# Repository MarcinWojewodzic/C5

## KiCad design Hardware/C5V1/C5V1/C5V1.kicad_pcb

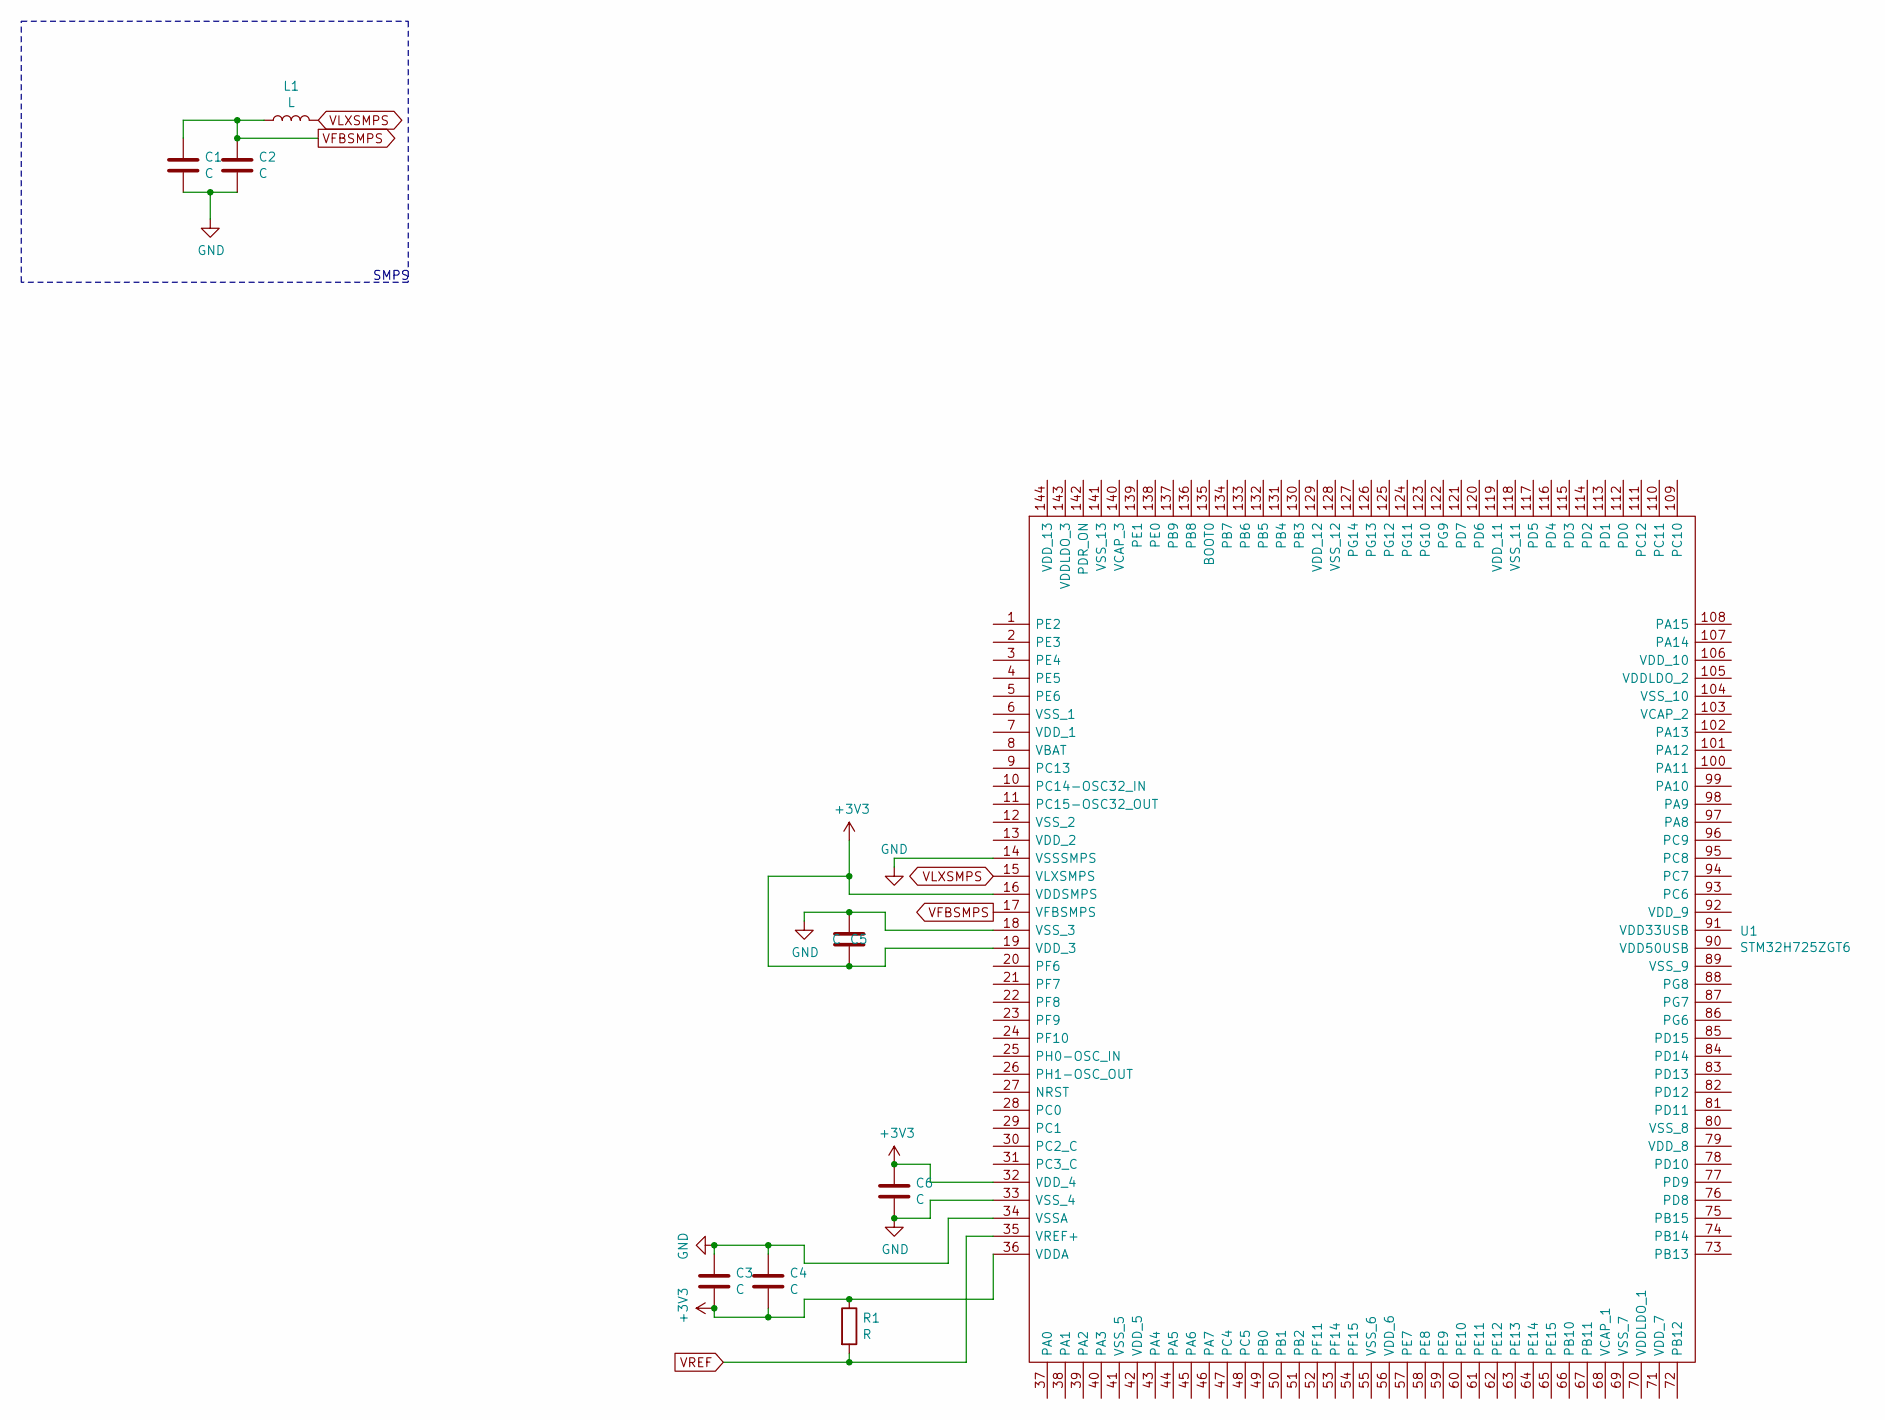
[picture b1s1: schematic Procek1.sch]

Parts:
C1, C2, C3, C4, C5, C6: C; C_0402_1005Metric
L1: L
R1: R; R_0402_1005Metric
U1: STM32H725ZGT6; QFP50P2200X2200X160-144N; Manufacturer_Part_Number STM32H725ZGT6; Mouser Part Number 511-STM32H725ZGT6

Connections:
+3V3: C3.2, C4.2, C5.2, C6.1, R1.1, U1.16 (VDDSMPS), U1.19 (VDD_3), U1.32 (VDD_4), U1.36 (VDDA); also elsewhere on the board
GND: C1.2, C2.2, C3.1, C4.1, C5.1, C6.2, U1.14 (VSSSMPS), U1.18 (VSS_3), U1.33 (VSS_4), U1.34 (VSSA); also elsewhere on the board
VFBSMPS: C1.1, C2.1, L1.1, U1.17 (VFBSMPS)
VLXSMPS: L1.2, U1.15 (VLXSMPS)
VREF: R1.2, U1.35 (VREF+)

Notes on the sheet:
SMPS

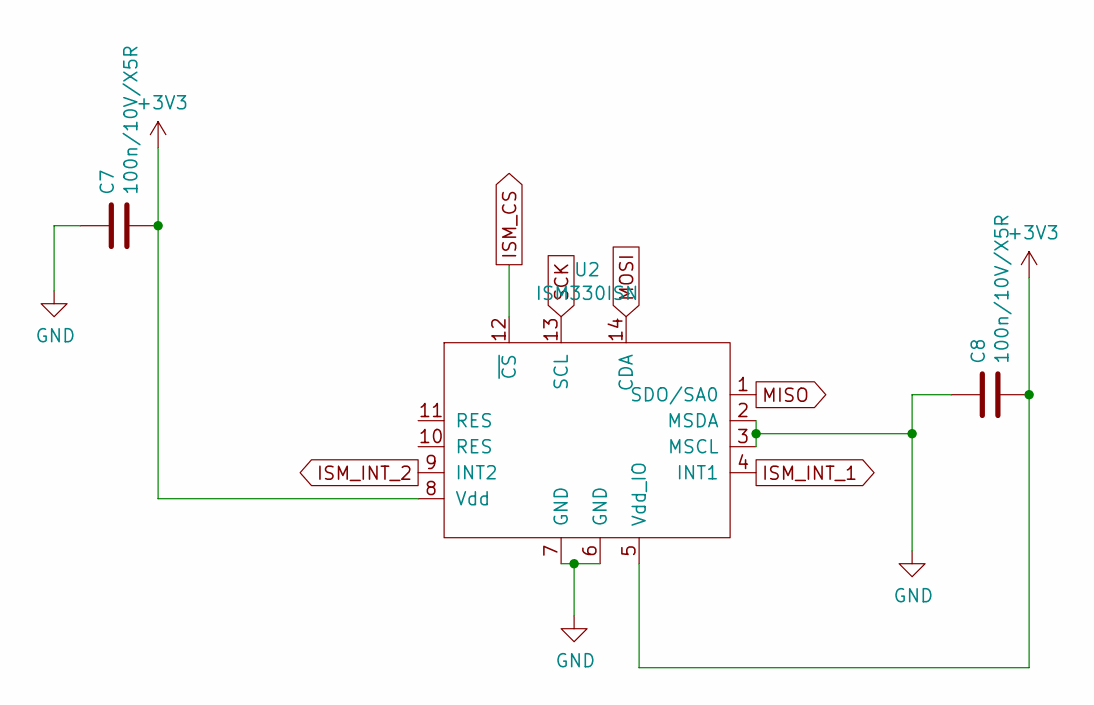
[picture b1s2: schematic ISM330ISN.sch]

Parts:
C7, C8: 100n/10V/X5R; C_0402_1005Metric
U2: ISM330ISN; LGA-14_3x2.5mm_P0.5mm_LayoutBorder3x4y

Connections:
+3V3: C7.2, C8.2, U2.5 (Vdd_IO), U2.8 (Vdd); also elsewhere on the board
GND: C7.1, C8.1, U2.2 (MSDA), U2.3 (MSCL), U2.6 (GND), U2.7 (GND); also elsewhere on the board
ISM_CS: U2.12 (~CS)
ISM_INT_1: U2.4 (INT1)
ISM_INT_2: U2.9 (INT2)
MISO: U2.1 (SDO/SA0)
MOSI: U2.14 (CDA)
SCK: U2.13 (SCL)

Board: 2 copper layers, 11 parts (0 on the bottom side), 4 nets, no tracks yet.

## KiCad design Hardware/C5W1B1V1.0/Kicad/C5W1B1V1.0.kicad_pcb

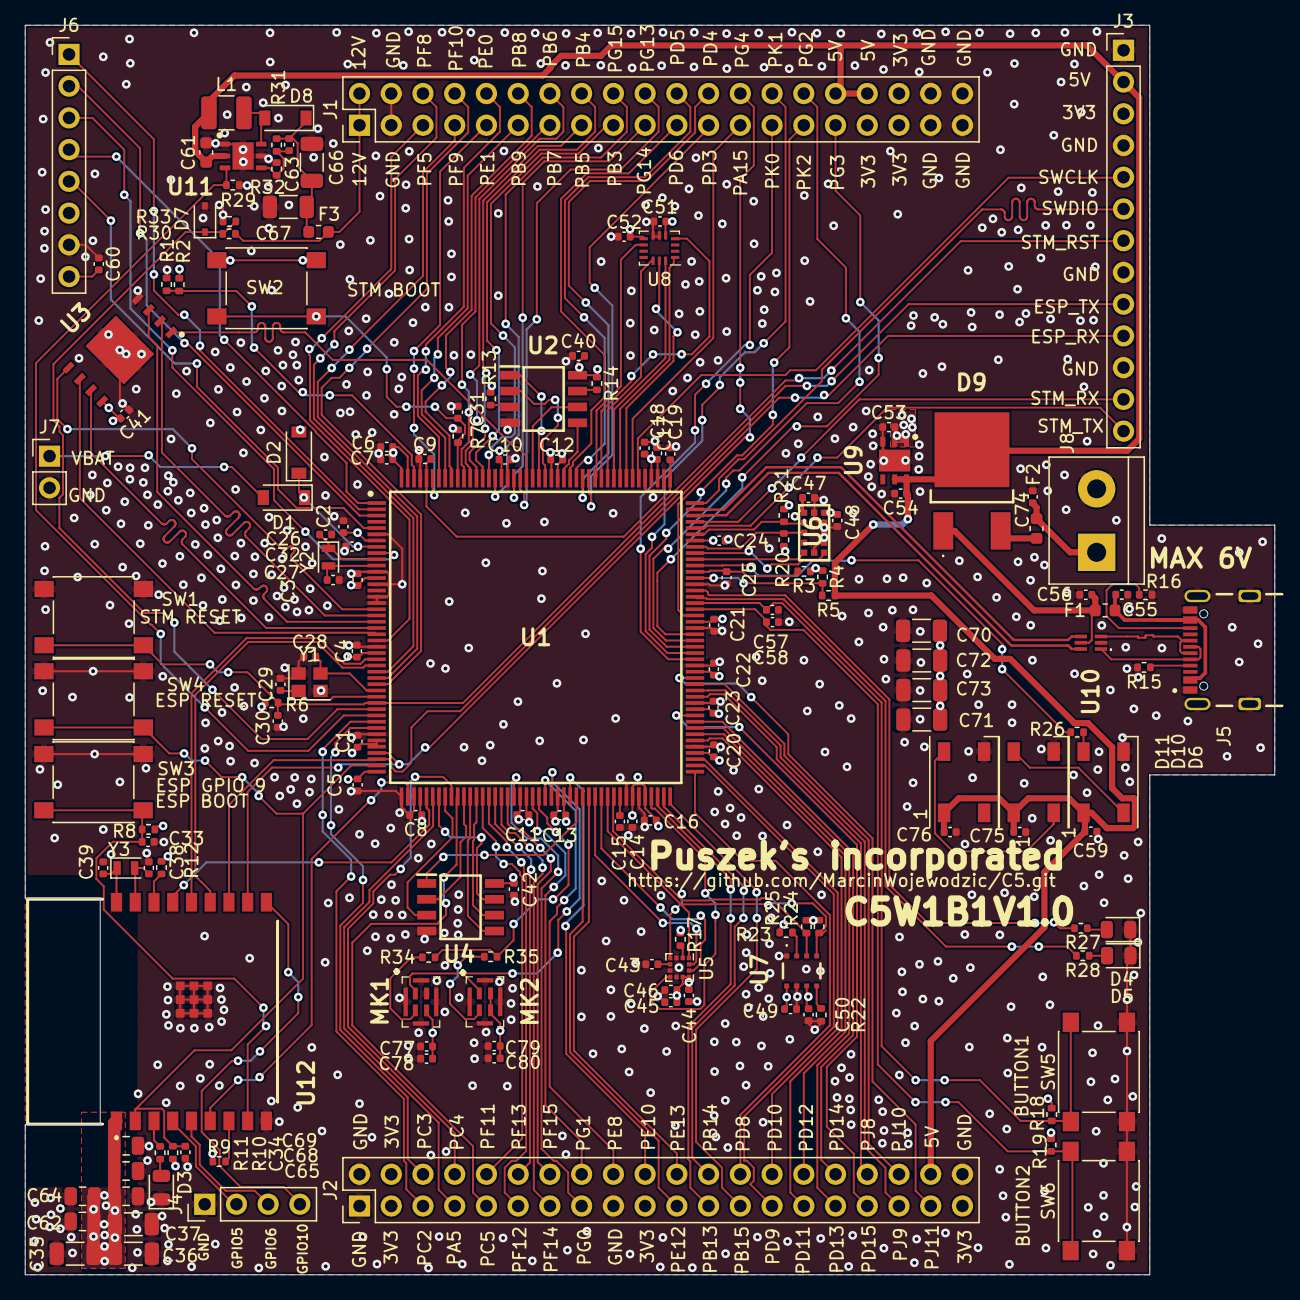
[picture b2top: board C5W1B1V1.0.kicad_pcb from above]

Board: 4 copper layers, 100.0 x 100.0 mm, 161 parts (0 on the bottom side), 167 nets.

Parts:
C1, C2, C3, C4, C5, C6, C7, C8, C10, C11, C12, C13, C14, C16, C17, C18, C20, C21, C22, C23, C24, C30, C31, C33, C34, C40, C41, C42, C44, C46, C47, C48, C49, C50, C51, C52, C57, C58, C59, C60, C75, C76, C77, C79: 100n/16V/X5R; C_0402_1005Metric
C9, C15, C19, C25, C32, C55, C56: 2.2u/16V/X5R; C_0402_1005Metric
C26, C27, C38, C39: 6p/16V/COG; C_0402_1005Metric
C28, C29: 8p/16V/COG; C_0402_1005Metric
C35, C36, C37, C70, C71, C72, C73: 100u/10V/X5R; C_1206_3216Metric
C43: 220n/16V/X5R; C_0402_1005Metric
C45: 10u/V/X5R/16V; C_0402_1005Metric
C53, C54, C74: 10u/6.3V/X5R; C_0402_1005Metric
C61: 10u/16V/X5R; C_0603_1608Metric
C62, C64, C65, C68, C69: 47u/10V/X5R; C_0805_2012Metric
C63: 185p/16V/C0G; C_0402_1005Metric
C66, C67: 10u/25V/X5R; C_1206_3216Metric
C78, C80: 1u/16V/X5R; C_0402_1005Metric
D1, D2: SD103AW-HE3_A-08; D_SOD-123
D3, D4, D5: LED; LED_0805_2012Metric
D6, D10, D11: WS2812B; LED_WS2812B_PLCC4_5.0x5.0mm_P3.2mm
D7: BZX384B3V3-E3-08; D_SOD-323
D8: PMEG4010CEGWX; D_SOD-123
D9: RBR10BM60AFHTL; RD3P175SNFRATL
F1, F2: 0686F2000-01; Fuse_0603_1608Metric
F3: SF-0603FP015F-2; Fuse_0603_1608Metric
J1, J2: Conn_02x20_Counter_Clockwise; PinHeader_2x20_P2.54mm_Vertical
J3: Conn_01x13_Male; PinHeader_1x13_P2.54mm_Vertical
J4: Conn_01x04; PinHeader_1x04_P2.54mm_Vertical
J5: USB4105GFA120; GCT_USB4105GFA120
J6: Conn_01x08_Male; PinHeader_1x08_P2.54mm_Vertical
J7: Conn_01x02_Male; PinHeader_1x02_P2.54mm_Vertical
J8: Conn_01x02_Male; TerminalBlock_bornier-2_P5.08mm
L1: CBC3225T470MR; L_1210_3225Metric
MK1, MK2: MP34DT05TR-A; MP34DT05TRA
R1, R2, R6, R7, R8, R9, R10, R11, R12, R13, R14, R17, R18, R19, R20, R21, R22, R23, R24, R25: 10k/5%/0.063W; R_0402_1005Metric
R3, R4, R5: 0R; R_0402_1005Metric
R15, R16: 5.1K/5%/0.063W; R_0402_1005Metric
R26, R27, R28: 470/5%/0.063W; R_0402_1005Metric
R29, R30, R32: 10K/5%/0.063W; R_0402_1005Metric
R31: 85.6K/5%/0.063W; R_0402_1005Metric
R33: 3.3K/5%/0.063W; R_0402_1005Metric
R34, R35: 100k/5%/0.063W; R_0402_1005Metric
SW1, SW2, SW3, SW4, SW5, SW6: SW_Push_Dual; SW_Push_1P1T_NO_6x6mm_H9.5mm
U1: STM32H735IGT6; QFP50P2600X2600X160-176N
U2: MB85RS512TPNF-G-JNERE1; SOIC127P600X175-8N
U3: W25N512GVEIG; SON127P800X600X80-9N-D
U4: APS6404L-3SQR-SN; SOIC127P600X175-8N
U5: LSM303AHTR; LGA-12_2x2mm_P0.5mm
U6: VL53L0CXV0DH_1; LGA12_1
U7: BME688
U8: ISM330ISN; Bosch_LGA-14_3x2.5mm_P0.5mm
U9: LD39200PU33R; SON95P300X300X100-7N-D
U10: USBLC6-2P6; USBLC62P6
U11: LMR62421XSD_NOPB; SON95P300X300X80-7N
U12: ESP32-C3-WROOM-02-N4; ESP32C3WROOM02N4
Y1: ECS-250-8-36CKM-TR3; Crystal_SMD_2520-4Pin_2.5x2.0mm
Y2, Y3: 830106545501; Crystal_SMD_2012-2Pin_2.0x1.2mm

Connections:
5V_EXT: D9.3, F2.1
5V_USB: C56.1, D9.1, F1.1, U10.5
12V_DC_V: D7.1, R30.1, R33.2, U1.34
12V_EN: R29.1, U1.35, U11.3
+3V3: C1.1, C2.1, C3.1, C4.1, C5.2, C6.2, C7.2, C8.1, C10.1, C11.1, C12.1, C13.1, C14.1, C16.1, C17.2, C18.1, C20.2, C21.1, C22.2, C23.2, C24.1, C35.2, C36.2, C37.2, C40.2, C41.2, C42.2, C44.2, C45.1, C46.1, C47.1, C48.2, C49.1, C50.1, C51.2, C52.2, C53.2, C60.2, C62.2, C64.2, C65.2, C68.2, C69.2, C70.2, C71.2, C72.2, C73.2, C77.1, C78.1, C79.1, C80.1, D2.2, J1.33, J1.35, J1.36, J2.3, J2.4, J2.19, J2.39, J3.3, J6.8, MK1.3, MK2.3, MK2.4, R2.1, R3.1, R4.1, R6.1, R8.1, R9.1, R10.1, R12.1, R13.1, R14.1, R17.1, R18.1, R19.1, R20.1, R21.1, R23.1, R24.1, R25.1, SW2.1, U1.7, U1.13, U1.25, U1.39, U1.40, U1.44, U1.48, U1.65, U1.71, U1.82, U1.84, U1.92, U1.99, U1.105, U1.113, U1.126, U1.135, U1.136, U1.152, U1.160, U1.175, U1.176, U2.8, U3.8, U4.8, U5.9, U5.10, U6.1, U6.11, U7.6, U7.8, U8.5, U8.8, U9.1, U9.2, U12.1
+5V: C54.1, C59.1, C61.1, C75.1, C76.1, D6.1, D9.2, D10.1, D11.1, J1.32, J1.34, J2.38, J3.2, L1.1, R5.1, U9.5, U9.6, U11.2
+12V: F3.1, J1.1, J1.2, R30.2
/Power/VBUS: C55.1, F1.2, J5.A4_B9, J5.B4_A9
/uC/VCAP3: C9.2, C19.2, U1.133, U1.172
BME688_SCL: R24.2, U1.78, U5.1, U7.4
BME688_SDA: R25.2, U1.79, U5.4, U7.3
BUTTON1: C57.2, R18.2, SW5.1, U1.116
BUTTON2: C58.2, R19.2, SW6.1, U1.115
DBG_RX: J3.10, U1.41, U12.11
DBG_TX: J3.9, U1.42, U12.12
DFSDM_CLK: MK1.1, MK2.1, U1.69
DFSDM_DATA: R34.2, R35.2, U1.67
ESP_GPIO5: J4.2, U12.4
ESP_GPIO6: J4.3, U12.5
ESP_GPIO10: J4.4, U12.10
ESP_RST: C34.2, R10.2, SW4.2, U1.43, U12.2
ESP_RX: U1.27, U12.13
ESP_TX: U1.26, U12.14
FLASH_IO0: U1.18, U3.5
FLASH_IO1: U1.19, U3.2
FLASH_IO2: U1.20, U3.3
FLASH_IO3: U1.21, U3.7
FLASH_NCS: U1.156, U3.1
FLASH_SCK: U1.22, U3.6
FRAM_CS: U1.154, U2.1
FRAM_MISO: U1.153, U2.2
FRAM_MOSI: U1.150, U2.5
FRAM_SCK: U1.155, U2.6
GND: C1.2, C2.2, C3.2, C4.2, C5.1, C6.1, C7.1, C8.2, C9.1, C10.2, C11.2, C12.2, C13.2, C14.2, C15.1, C16.2, C17.1, C18.2, C19.1, C20.1, C21.2, C22.1, C23.1, C24.2, C25.2, C26.1, C27.2, C28.1, C29.2, C30.1, C31.2, C32.2, C33.1, C34.1, C35.1, C36.1, C37.1, C38.2, C39.1, C40.1, C41.1, C42.1, C43.2, C44.1, C45.2, C46.2, C47.2, C48.1, C49.2, C50.2, C51.1, C52.1, C53.1, C54.2, C55.2, C56.2, C57.1, C58.1, C59.2, C60.1, C61.2, C62.1, C64.1, C65.1, C66.2, C67.2, C68.1, C69.1, C70.1, C71.1, C72.1, C73.1, C74.2, C75.2, C76.2, C77.2, C78.2, C79.2, C80.2, D3.1, D4.1, D5.1, D6.3, D7.2, D10.3, D11.3, J1.3, J1.4, J1.37, J1.38, J1.39, J1.40, J2.1, J2.2, J2.17, J2.40, J3.1, J3.4, J3.8, J3.11, J4.1, J5.A1_B12, J5.B1_A12, J5.SH1, J5.SH2, J5.SH3, J5.SH4, J6.7, J7.2, J8.2, MK1.4, MK1.5, MK1.6, MK1.7, MK1.8, MK2.5, MK2.6, MK2.7, MK2.8, R1.2, R7.1, R15.2, R16.2, R22.2, R29.2, R32.2, R33.1, SW1.1, SW3.1, SW4.1, SW5.2, SW6.2, U1.6, U1.12, U1.14, U1.16, U1.17, U1.24, U1.38, U1.45, U1.47, U1.64, U1.70, U1.81, U1.83, U1.93, U1.100, U1.106, U1.112, U1.119, U1.134, U1.137, U1.151, U1.159, U1.173, U2.4, U3.4, U3.9, U4.4, U5.3, U5.6, U5.8, U6.2, U6.3, U6.4, U6.6, U6.12, U7.1, U7.7, U8.6, U8.7, U9.3, U9.7, U10.2, U11.1, U11.5, U11.7, U12.9, U12.19, U12.20, U12.21, U12.22, U12.23, U12.24, U12.25, U12.26, U12.27, Y1.2, Y1.4
ISM330_CS: U1.143, U8.12
ISM330_INT1: U1.144, U8.4
ISM330_INT2: U1.145, U8.9
ISM330_MISO: U1.141, U8.1
ISM330_MOSI: U1.142, U8.14
ISM330_SCK: U1.140, U8.13
LED1: R27.2, U1.118
LED2: R28.2, U1.117
LSM303_INT1: U1.76, U5.12
LSM303_INT2: U1.77, U5.11
LSM303_INT_MAG: U1.85, U5.7
unnamed: C15.2, U1.80
unnamed: C25.1, R3.2, U1.121
unnamed: C26.2, U1.10, Y2.1
unnamed: C27.1, U1.11, Y2.2
unnamed: C28.2, U1.31, Y1.3
unnamed: C29.1, U1.32, Y1.1
unnamed: C31.1, R7.2, SW2.2, U1.167
unnamed: C32.1, D1.1, D2.1, U1.8
unnamed: C33.2, R8.2, SW3.2, U12.8
unnamed: C38.1, U12.17, Y3.2
unnamed: C39.2, U12.18, Y3.1
unnamed: C43.1, U5.5
unnamed: C63.1, R31.2, R32.1, U11.4
unnamed: C63.2, C66.1, C67.1, D8.1, F3.2, R31.1
unnamed: C74.1, F2.2, J8.1
unnamed: D3.2, R11.1
unnamed: D4.2, R27.1
unnamed: D5.2, R28.1
unnamed: D6.4, R26.1
unnamed: D8.2, L1.2, U11.6
unnamed: D10.2, D11.4
unnamed: D6.2, D10.4
unnamed: J5.A5, R15.1
unnamed: J5.A6, J5.B6, U10.3
unnamed: J5.A7, J5.B7, U10.1
unnamed: J5.B5, R16.1
unnamed: MK1.2, R34.1
unnamed: MK2.2, R35.1
unnamed: R1.1, R2.2, U1.174
unnamed: R4.2, R5.2, U1.120
unnamed: R9.2, U12.7
unnamed: R11.2, U12.3
unnamed: R12.2, U12.16
unnamed: R13.2, U2.3
unnamed: R14.2, U2.7
unnamed: R17.2, U5.2
unnamed: R22.1, U7.5
unnamed: R23.2, U7.2
PA5: J2.7, U1.50
PA15: J1.25, U1.139
PB3: J1.17, U1.162
PB4: J1.16, U1.163
PB5: J1.15, U1.164
PB6: J1.14, U1.165
PB7: J1.13, U1.166
PB8: J1.12, U1.168
PB9: J1.11, U1.169
PB13: J2.23, U1.86
PB14: J2.24, U1.87
PB15: J2.25, U1.88
PC2: J2.5, U1.36
PC3: J2.6, U1.37
PC4: J2.8, U1.53
PC5: J2.9, U1.54
PD3: J1.23, U1.146
PD4: J1.24, U1.147
PD5: J1.22, U1.148
PD6: J1.21, U1.149
PD8: J2.26, U1.89
PD9: J2.27, U1.90
PD10: J2.28, U1.91
PD11: J2.29, U1.94
PD12: J2.30, U1.95
PD13: J2.31, U1.96
PD14: J2.32, U1.97
PD15: J2.33, U1.98
PE0: J1.10, U1.170
PE1: J1.9, U1.171
PE8: J2.18, U1.68
PE10: J2.20, U1.72
PE12: J2.21, U1.74
PE13: J2.22, U1.75
PF5: J1.5, U1.23
PF8: J1.6, U1.28
PF9: J1.7, U1.29
PF10: J1.8, U1.30
PF11: J2.10, U1.58
PF12: J2.11, U1.59
PF13: J2.12, U1.60
PF14: J2.13, U1.61
PF15: J2.14, U1.62
PG0: J2.15, U1.63
PG1: J2.16, U1.66
PG2: J1.30, U1.110
PG3: J1.31, U1.111
PG4: J1.26, U1.114
PG13: J1.20, U1.157
PG14: J1.19, U1.158
PG15: J1.18, U1.161
PJ8: J2.34, U1.101
PJ9: J2.35, U1.102
PJ10: J2.36, U1.103
PJ11: J2.37, U1.104
PK0: J1.27, U1.107
PK1: J1.28, U1.108
PK2: J1.29, U1.109
PSAM_SCK: U1.57, U4.6
PSRAM_IO0: U1.56, U4.5
PSRAM_IO1: U1.55, U4.2
PSRAM_IO2: U1.52, U4.3
PSRAM_IO3: U1.51, U4.7
PSRAM_NCS: U1.73, U4.1
SSD1331_CS: J6.3, U1.9
SSD1331_DC: J6.2, U1.3
SSD1331_MOSI: J6.5, U1.5
SSD1331_RES: J6.1, U1.2
SSD1331_SCK: J6.4, U1.1
STM_DBG_RX: J3.12, U1.129
STM_DBG_TX: J3.13, U1.128
STM_ESP_PIN1: U1.46, U12.6
STM_ESP_PIN2: U1.49, U12.15
STM_NRS: C30.2, J3.7, R6.2, SW1.2, U1.33
SWCLK: J3.5, U1.138
SWDIO: J3.6, U1.132
USB_D+: U1.131, U10.4
USB_D-: U1.130, U10.6
VBAT: D1.2, J7.1
VL53_EN: U1.124, U6.5
VL53_INT: U1.123, U6.7
VL53_SCL: R21.2, U1.127, U6.10
VL53_SDA: R20.2, U1.125, U6.9
WS2812: R26.2, U1.122

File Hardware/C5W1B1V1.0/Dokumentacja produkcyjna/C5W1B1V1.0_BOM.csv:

"Id";"Oznaczenie";"Obudowa";"Ilość";"Oznaczenie";"Dostawca i numer artykułu";
1;"C73,C72,C71,C70,C37,C36,C35";"C_1206_3216Metric";7;"100u/10V/X5R";;;
2;"C77,C79,C75,C76,C34,C60,C59,C58,C57,C33,C41,C50,C49,C46,C44,C52,C51,C48,C47,C42,C40,C31,C30,C24,C23,C22,C21,C20,C18,C17,C16,C14,C13,C12,C11,C10,C8,C7,C6,C5,C4,C3,C2,C1";"C_0402_1005Metric";44;"100n/16V/X5R";;;
3;"C78,C80";"C_0402_1005Metric";2;"1u/16V/X5R";;;
4;"D11,D10,D6";"LED_WS2812B_PLCC4_5.0x5.0mm_P3.2mm";3;"WS2812B";;;
5;"MK1,MK2";"MP34DT05TRA";2;"MP34DT05TR-A";;;
6;"R34,R35";"R_0402_1005Metric";2;"100k/5%/0.063W";;;
7;"F2,F1";"Fuse_0603_1608Metric";2;"0686F2000-01";;;
8;"J8";"TerminalBlock_bornier-2_P5.08mm";1;"Conn_01x02_Male";;;
9;"D9";"RD3P175SNFRATL";1;"RBR10BM60AFHTL";;;
10;"C74,C54,C53";"C_0402_1005Metric";3;"10u/6.3V/X5R";;;
11;"U9";"SON95P300X300X100-7N-D";1;"LD39200PU33R";;;
12;"R11,R10,R19,R18,R12,R9,R8,R25,R24,R23,R22,R21,R20,R17,R14,R13,R7,R6,R2,R1";"R_0402_1005Metric";20;"10k/5%/0.063W";;;
13;"J4";"PinHeader_1x04_P2.54mm_Vertical";1;"Conn_01x04";;;
14;"D3,D5,D4";"LED_0805_2012Metric";3;"LED";;;
15;"U12";"ESP32C3WROOM02N4";1;"ESP32-C3-WROOM-02-N4";;;
16;"C69,C68,C65,C64,C62";"C_0805_2012Metric";5;"47u/10V/X5R";;;
17;"L1";"L_1210_3225Metric";1;"CBC3225T470MR";;;
18;"J6";"PinHeader_1x08_P2.54mm_Vertical";1;"Conn_01x08_Male";;;
19;"R33";"R_0402_1005Metric";1;"3.3K/5%/0.063W";;;
20;"J7";"PinHeader_1x02_P2.54mm_Vertical";1;"Conn_01x02_Male";;;
21;"J1,J2";"PinHeader_2x20_P2.54mm_Vertical";2;"Conn_02x20_Counter_Clockwise";;;
22;"R30,R29,R32";"R_0402_1005Metric";3;"10K/5%/0.063W";;;
23;"D7";"D_SOD-323";1;"BZX384B3V3-E3-08";;;
24;"SW1,SW6,SW5,SW4,SW3,SW2";"SW_Push_1P1T_NO_6x6mm_H9.5mm";6;"SW_Push_Dual";;;
25;"C66,C67";"C_1206_3216Metric";2;"10u/25V/X5R";;;
26;"F3";"Fuse_0603_1608Metric";1;"SF-0603FP015F-2";;;
27;"R31";"R_0402_1005Metric";1;"85.6K/5%/0.063W";;;
28;"U11";"SON95P300X300X80-7N";1;"LMR62421XSD_NOPB";;;
29;"D8";"D_SOD-123";1;"PMEG4010CEGWX";;;
30;"C63";"C_0402_1005Metric";1;"185p/16V/C0G";;;
31;"C61";"C_0603_1608Metric";1;"10u/16V/X5R";;;
32;"R28,R27,R26";"R_0402_1005Metric";3;"470/5%/0.063W";;;
33;"U1";"QFP50P2600X2600X160-176N";1;"STM32H735IGT6";;;
34;"J3";"PinHeader_1x13_P2.54mm_Vertical";1;"Conn_01x13_Male";;;
35;"D2,D1";"D_SOD-123";2;"SD103AW-HE3_A-08";;;
36;"Y3,Y2";"Crystal_SMD_2012-2Pin_2.0x1.2mm";2;"830106545501";;;
37;"C39,C38,C27,C26";"C_0402_1005Metric";4;"6p/16V/COG";;;
38;"U3";"SON127P800X600X80-9N-D";1;"W25N512GVEIG";;;
39;"C29,C28";"C_0402_1005Metric";2;"8p/16V/COG";;;
40;"Y1";"Crystal_SMD_2520-4Pin_2.5x2.0mm";1;"ECS-250-8-36CKM-TR3";;;
41;"U7";"BME688";1;"BME688";;;
42;"U8";"Bosch_LGA-14_3x2.5mm_P0.5mm";1;"ISM330ISN";;;
43;"U5";"LGA-12_2x2mm_P0.5mm";1;"LSM303AHTR";;;
44;"C56,C55,C32,C25,C19,C15,C9";"C_0402_1005Metric";7;"2.2u/16V/X5R";;;
45;"R16,R15";"R_0402_1005Metric";2;"5.1K/5%/0.063W";;;
46;"C45";"C_0402_1005Metric";1;"10u/V/X5R/16V";;;
47;"C43";"C_0402_1005Metric";1;"220n/16V/X5R";;;
48;"J5";"GCT_USB4105GFA120";1;"USB4105GFA120";;;
49;"U10";"USBLC62P6";1;"USBLC6-2P6";;;
50;"U6";"LGA12_1";1;"VL53L0CXV0DH_1";;;
51;"U4";"SOIC127P600X175-8N";1;"APS6404L-3SQR-SN";;;
52;"U2";"SOIC127P600X175-8N";1;"MB85RS512TPNF-G-JNERE1";;;
53;"R5,R4,R3";"R_0402_1005Metric";3;"0R";;;

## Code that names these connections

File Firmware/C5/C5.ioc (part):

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Mcu.Name=STM32H735IGTx
Mcu.Package=LQFP176
Mcu.UserName=STM32H735IGTx
PA0.Mode=Asynchronous
PA0.Signal=UART4_TX
PA1.Mode=Asynchronous
PA1.Signal=UART4_RX
PA10.Mode=Asynchronous
PA10.Signal=USART1_RX
PA11.Mode=Host_FS
PA11.Signal=USB_OTG_HS_DM
PA12.Mode=Host_FS
PA12.Signal=USB_OTG_HS_DP
PA13(JTMS/SWDIO).Mode=Serial_Wire
PA13(JTMS/SWDIO).Signal=DEBUG_JTMS-SWDIO
PA14(JTCK/SWCLK).Mode=Serial_Wire
PA14(JTCK/SWCLK).Signal=DEBUG_JTCK-SWCLK
PA2.GPIOParameters=GPIO_Speed,PinState,GPIO_Label
PA2.GPIO_Label=ESP_RST
PA2.GPIO_Speed=GPIO_SPEED_FREQ_VERY_HIGH
PA2.PinState=GPIO_PIN_SET
PA2.Signal=GPIO_Output
PA3.GPIOParameters=GPIO_Label
PA3.GPIO_Label=STM_ESP_PIN1
PA3.Signal=GPIO_Input
PA4.GPIOParameters=GPIO_Label
PA4.GPIO_Label=STM_ESP_PIN2
PA4.Signal=GPIO_Input
PA6.Mode=OCTOSPI1_IOL_Port1L
PA6.Signal=OCTOSPIM_P1_IO3
PA7.Mode=OCTOSPI1_IOL_Port1L
PA7.Signal=OCTOSPIM_P1_IO2
PA8.Mode=I2C
PA8.Signal=I2C3_SCL
PA9.Mode=Asynchronous
PA9.Signal=USART1_TX
PB0.Mode=OCTOSPI1_IOL_Port1L
PB0.Signal=OCTOSPIM_P1_IO1
PB1.Mode=OCTOSPI1_IOL_Port1L
PB1.Signal=OCTOSPIM_P1_IO0
PB10.Mode=I2C
PB10.Signal=I2C2_SCL
PB11.Mode=I2C
PB11.Signal=I2C2_SDA
PB12.GPIOParameters=GPIO_Label
PB12.GPIO_Label=LSM303_INT_MAG
PB12.Signal=GPXTI12
PB2.Mode=O1_P1_CLK
PB2.Signal=OCTOSPIM_P1_CLK
PB6.Mode=I2C
PB6.Signal=I2C1_SCL
PB7.Mode=I2C
PB7.Signal=I2C1_SDA
PC10.Mode=Full_Duplex_Master
PC10.Signal=SPI3_SCK
PC11.Mode=Full_Duplex_Master
PC11.Signal=SPI3_MISO
PC12.Mode=Full_Duplex_Master
PC12.Signal=SPI3_MOSI
PC13.GPIOParameters=PinState,GPIO_Label
PC13.GPIO_Label=SSD1331_CS
PC13.PinState=GPIO_PIN_SET
PC13.Signal=GPIO_Output
PC14-OSC32_IN.Mode=LSE-External-Oscillator
PC14-OSC32_IN.Signal=RCC_OSC32_IN
PC15-OSC32_OUT.Mode=LSE-External-Oscillator
PC15-OSC32_OUT.Signal=RCC_OSC32_OUT
PC4.Signal=S_CKIN2DFSDM1
PC6.GPIOParameters=GPIO_Label
PC6.GPIO_Label=WS2812
PC6.Signal=S_TIM3_CH1
PC7.GPIOParameters=GPIO_Label
PC7.GPIO_Label=VL53_INT
PC7.Signal=GPXTI7
PC8.GPIOParameters=GPIO_Label
PC8.GPIO_Label=VL53_EN
PC8.Signal=GPXTI8
PC9.Mode=I2C
PC9.Signal=I2C3_SDA
PD0.GPIOParameters=GPIO_Speed,PinState,GPIO_Label
PD0.GPIO_Label=ISM330_CS
PD0.GPIO_Speed=GPIO_SPEED_FREQ_VERY_HIGH
PD0.PinState=GPIO_PIN_SET
PD0.Signal=GPIO_Output
PD1.GPIOParameters=GPIO_Label
PD1.GPIO_Label=ISM330_INT1
PD1.Signal=GPXTI1
PD2.GPIOParameters=GPIO_Label
PD2.GPIO_Label=ISM330_INT2
PD2.Signal=GPXTI2
PD7.Mode=Full_Duplex_Master
PD7.Signal=SPI1_MOSI
PE11.Mode=OCTOSPI1_Port1_NCS
PE11.Signal=OCTOSPIM_P1_NCS
PE14.GPIOParameters=GPIO_Label
PE14.GPIO_Label=LSM303_INT2
PE14.Signal=GPXTI14
PE15.GPIOParameters=GPIO_Label
PE15.GPIO_Label=LSM303_INT1
PE15.Signal=GPXTI15
PE2.Mode=TX_Only_Simplex_Unidirect_Master
PE2.Signal=SPI4_SCK
PE3.GPIOParameters=GPIO_Label
PE3.GPIO_Label=SSD1331_RES
PE3.Signal=GPIO_Output
PE4.GPIOParameters=GPIO_Speed,PinState,GPIO_Label
PE4.GPIO_Label=SSD1331_DC
PE4.GPIO_Speed=GPIO_SPEED_FREQ_VERY_HIGH
PE4.PinState=GPIO_PIN_SET
PE4.Signal=GPIO_Output
PE6.Mode=TX_Only_Simplex_Unidirect_Master
PE6.Signal=SPI4_MOSI
PE7.GPIOParameters=GPIO_Speed
PE7.GPIO_Speed=GPIO_SPEED_FREQ_VERY_HIGH
PE7.Signal=S_DATAIN2DFSDM1
PE9.GPIOParameters=GPIO_Speed
PE9.GPIO_Speed=GPIO_SPEED_FREQ_VERY_HIGH
PE9.Signal=S_CKOUTDFSDM1
PF0.Mode=OCTOSPI2_IOL_Port2L
PF0.Signal=OCTOSPIM_P2_IO0
PF1.Mode=OCTOSPI2_IOL_Port2L
PF1.Signal=OCTOSPIM_P2_IO1
PF2.Mode=OCTOSPI2_IOL_Port2L
PF2.Signal=OCTOSPIM_P2_IO2
PF3.Mode=OCTOSPI2_IOL_Port2L
PF3.Signal=OCTOSPIM_P2_IO3
PF4.Mode=O2_P2_CLK
PF4.Signal=OCTOSPIM_P2_CLK
PF6.Mode=Asynchronous
PF6.Signal=UART7_RX
PF7.Mode=Asynchronous
PF7.Signal=UART7_TX
PG10.GPIOParameters=GPIO_Label
PG10.GPIO_Label=FRAM_CS
PG10.Signal=GPIO_Output
PG11.Mode=Full_Duplex_Master
PG11.Signal=SPI1_SCK
PG12.Mode=OCTOSPI2_Port2_NCS
PG12.Signal=OCTOSPIM_P2_NCS
PG7.GPIOParameters=GPIO_Speed,GPIO_Label
PG7.GPIO_Label=LED2
PG7.GPIO_Speed=GPIO_SPEED_FREQ_VERY_HIGH
PG7.Signal=GPIO_Output
PG8.GPIOParameters=GPIO_Speed,GPIO_Label
PG8.GPIO_Label=LED1
PG8.GPIO_Speed=GPIO_SPEED_FREQ_VERY_HIGH
PG8.Signal=GPIO_Output
PG9.Mode=Full_Duplex_Master
PG9.Signal=SPI1_MISO
PH0-OSC_IN.Mode=HSE-External-Oscillator
PH0-OSC_IN.Signal=RCC_OSC_IN
PH1-OSC_OUT.Mode=HSE-External-Oscillator
PH1-OSC_OUT.Signal=RCC_OSC_OUT
RCC.SYSCLKFreq_VALUE=550000000
RCC.SYSCLKSource=RCC_SYSCLKSOURCE_PLLCLK
board=custom

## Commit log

2023-04-23 Dodano początkowe zasilanie
2023-05-07 Dodano schemat ISN
2024-06-08 Podstawowy schemat
2024-06-27 Linie PC0-PE13
2024-06-30 Rozlana masa
2024-06-30 Dodano opisy
2024-07-05 End PCB
2024-11-08 Skończono PCB
2024-11-15 Dodano mikrofony i więcej WS2812B
2024-11-16 Drobne poprawki
